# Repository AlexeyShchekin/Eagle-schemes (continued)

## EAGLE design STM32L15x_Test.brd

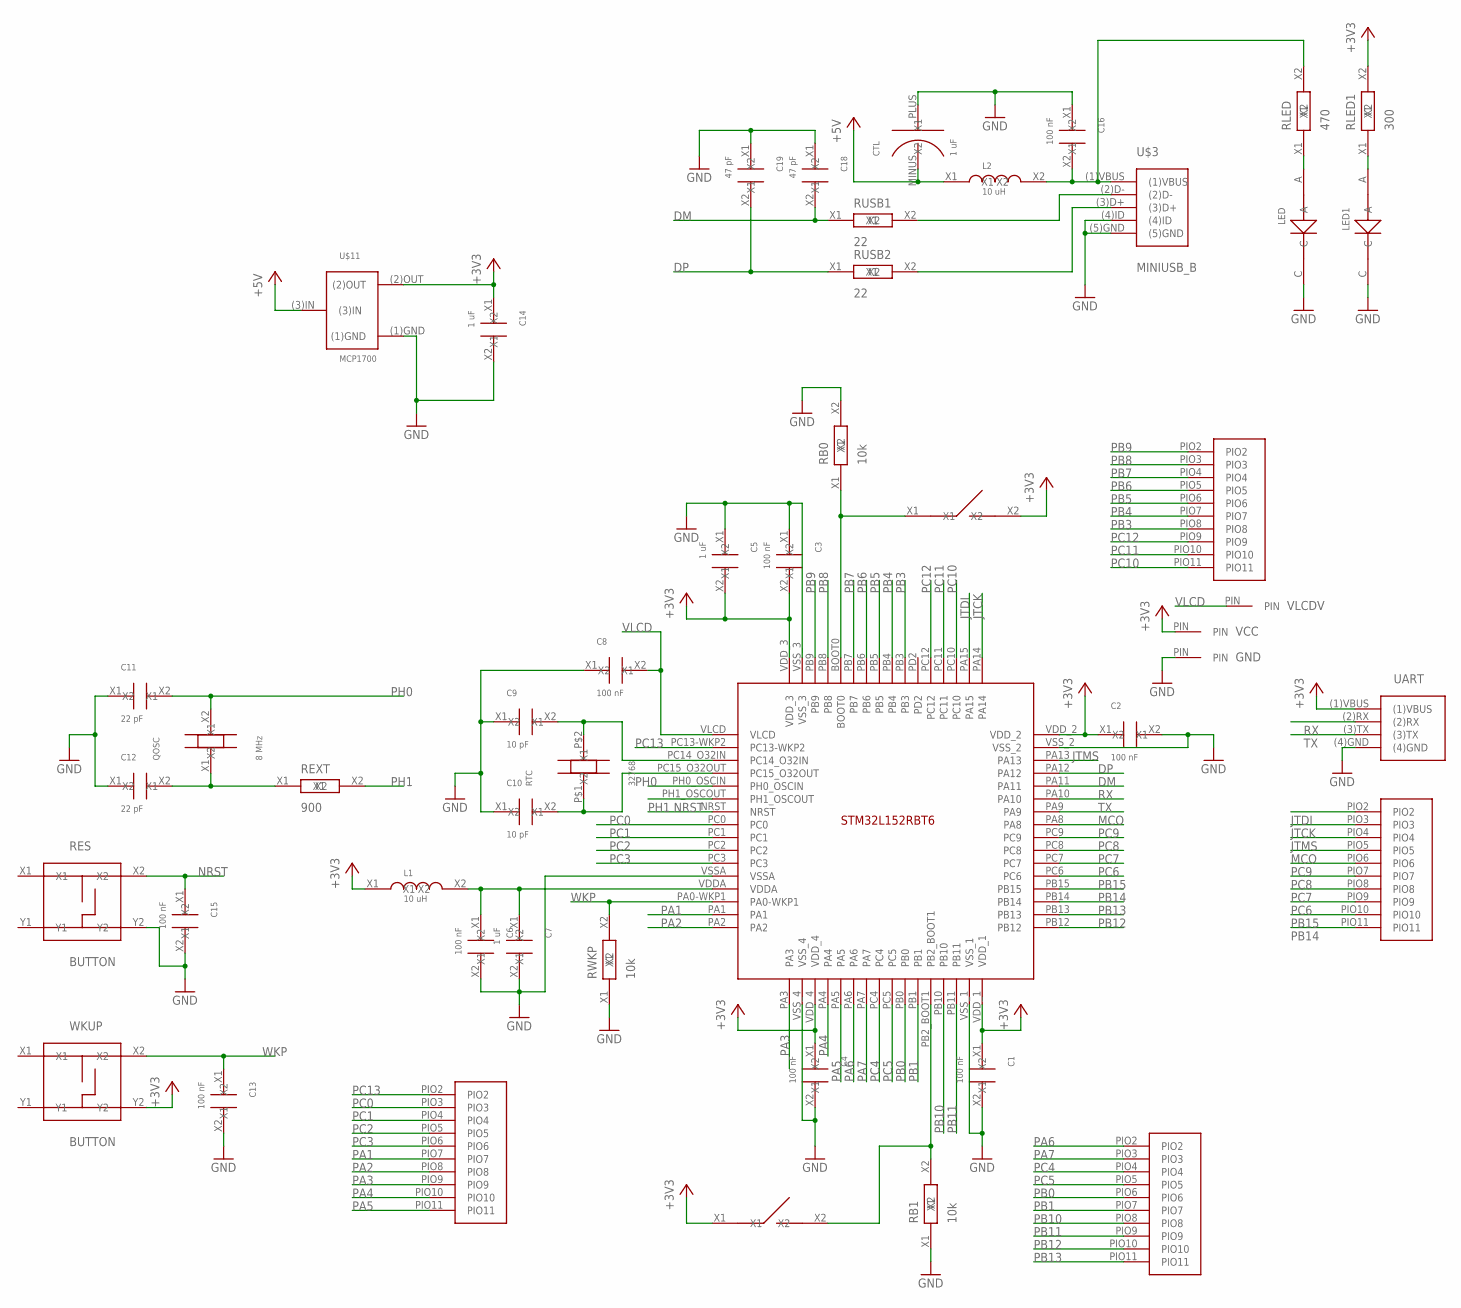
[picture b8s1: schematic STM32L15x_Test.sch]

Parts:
C1, C2, C3, C4, C6, C8, C13, C15, C16: 100 nF; SMD_2.1X1.25
C5, C7, C14: 1 uF; SMD_2.1X1.25
C9, C10: 10 pF; SMD_2.1X1.25
C11, C12: 22 pF; SMD_2.1X1.25
C18, C19: 47 pF; SMD_2.1X1.25
CTL: 1 uF; C_SMD_TA_A
GND: PIN
L1, L2: 10 uH; SMD_2.1X1.25
LED, LED1: LED0805; SMD0805
QOSC: 8 MHz; QUARTZ_SMD
RB0, RB1: 10k; SMD_2.1X1.25
RES: BUTTON
REXT: 900; SMD_2.1X1.25
RLED: 470; SMD_2.1X1.25
RLED1: 300; SMD_2.1X1.25
RTC: 32768; QUARTZ_CYL
RUSB1, RUSB2: 22; SMD_2.1X1.25
RWKP: 10k; SMD_2.1X1.25
U$1: STM32L15XRBT6; STM32L152RBT6
U$2, U$5, U$6, U$7: PIO_10
U$3: MINIUSB_B
U$8, U$9: DIP_1
U$11: MCP1700
UART: USART
VCC: PIN
VLCDV: PIN
WKUP: BUTTON

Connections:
+3V3: C1.X1, C2.X1, C3.X2, C4.X1, C5.X2, C14.X1, L1.X1, RLED1.X2, U$1.VDD_1, U$1.VDD_2, U$1.VDD_3, U$1.VDD_4, U$8.X2, U$9.X1, U$11.(2)OUT, UART.(1)VBUS, VCC.PIN, WKUP.Y2
+5V: CTL.MINUS (X1), L2.X1, U$11.(3)IN
BOOT0: RB0.X1, U$1.BOOT0, U$8.X1
BOOT1: RB1.X2, U$1.PB2_BOOT1, U$9.X2
DM: C18.X2, RUSB1.X1, U$1.PA11
DP: C19.X2, RUSB2.X1, U$1.PA12
GND: C1.X2, C2.X2, C3.X1, C4.X2, C5.X1, C6.X2, C7.X2, C8.X1, C9.X1, C10.X1, C11.X1, C12.X1, C13.X2, C14.X2, C15.X2, C16.X1, C18.X1, C19.X1, CTL.PLUS (X2), GND.PIN, LED.C, LED1.C, RB0.X2, RB1.X1, RES.Y2, RWKP.X1, U$1.VSSA, U$1.VSS_1, U$1.VSS_2, U$1.VSS_3, U$1.VSS_4, U$3.(4)ID, U$3.(5)GND, U$11.(1)GND, UART.(4)GND
JTCK: U$1.PA14, U$6.PIO3
JTDI: U$1.PA15, U$6.PIO2
JTMS: U$1.PA13, U$6.PIO4
MCO: U$1.PA8, U$6.PIO5
unnamed: C6.X1, C7.X1, L1.X2, U$1.VDDA
unnamed: C9.X2, RTC.P$2 (X2), U$1.PC14_O32IN
unnamed: C10.X2, RTC.P$1 (X1), U$1.PC15_O32OUT
unnamed: C12.X2, QOSC.X1, REXT.X1
unnamed: C16.X2, L2.X2, RLED.X2, U$3.(1)VBUS
unnamed: RUSB1.X2, U$3.(2)D-
unnamed: RUSB2.X2, U$3.(3)D+
unnamed: LED.A, RLED.X1
unnamed: LED1.A, RLED1.X1
NRST: C15.X1, RES.X2, U$1.NRST
PA1: U$1.PA1, U$2.PIO7
PA2: U$1.PA2, U$2.PIO8
PA3: U$1.PA3, U$2.PIO9
PA4: U$1.PA4, U$2.PIO10
PA5: U$1.PA5, U$2.PIO11
PA6: U$1.PA6, U$5.PIO2
PA7: U$1.PA7, U$5.PIO3
PB0: U$1.PB0, U$5.PIO6
PB1: U$1.PB1, U$5.PIO7
PB3: U$1.PB3, U$7.PIO8
PB4: U$1.PB4, U$7.PIO7
PB5: U$1.PB5, U$7.PIO6
PB6: U$1.PB6, U$7.PIO5
PB7: U$1.PB7, U$7.PIO4
PB8: U$1.PB8, U$7.PIO3
PB9: U$1.PB9, U$7.PIO2
PB10: U$1.PB10, U$5.PIO8
PB11: U$1.PB11, U$5.PIO9
PB12: U$1.PB12, U$5.PIO10
PB13: U$1.PB13, U$5.PIO11
PB14: U$1.PB14, U$6.PIO11
PB15: U$1.PB15, U$6.PIO10
PC0: U$1.PC0, U$2.PIO3
PC1: U$1.PC1, U$2.PIO4
PC2: U$1.PC2, U$2.PIO5
PC3: U$1.PC3, U$2.PIO6
PC4: U$1.PC4, U$5.PIO4
PC5: U$1.PC5, U$5.PIO5
PC6: U$1.PC6, U$6.PIO9
PC7: U$1.PC7, U$6.PIO8
PC8: U$1.PC8, U$6.PIO7
PC9: U$1.PC9, U$6.PIO6
PC10: U$1.PC10, U$7.PIO11
PC11: U$1.PC11, U$7.PIO10
PC12: U$1.PC12, U$7.PIO9
PC13: U$1.PC13-WKP2, U$2.PIO2
PH0: C11.X2, QOSC.X2, U$1.PH0_OSCIN
PH1: REXT.X2, U$1.PH1_OSCOUT
RX: U$1.PA10, UART.(2)RX
TX: U$1.PA9, UART.(3)TX
VLCD: C8.X2, U$1.VLCD, VLCDV.PIN
WKP: C13.X1, RWKP.X2, U$1.PA0-WKP1, WKUP.X2

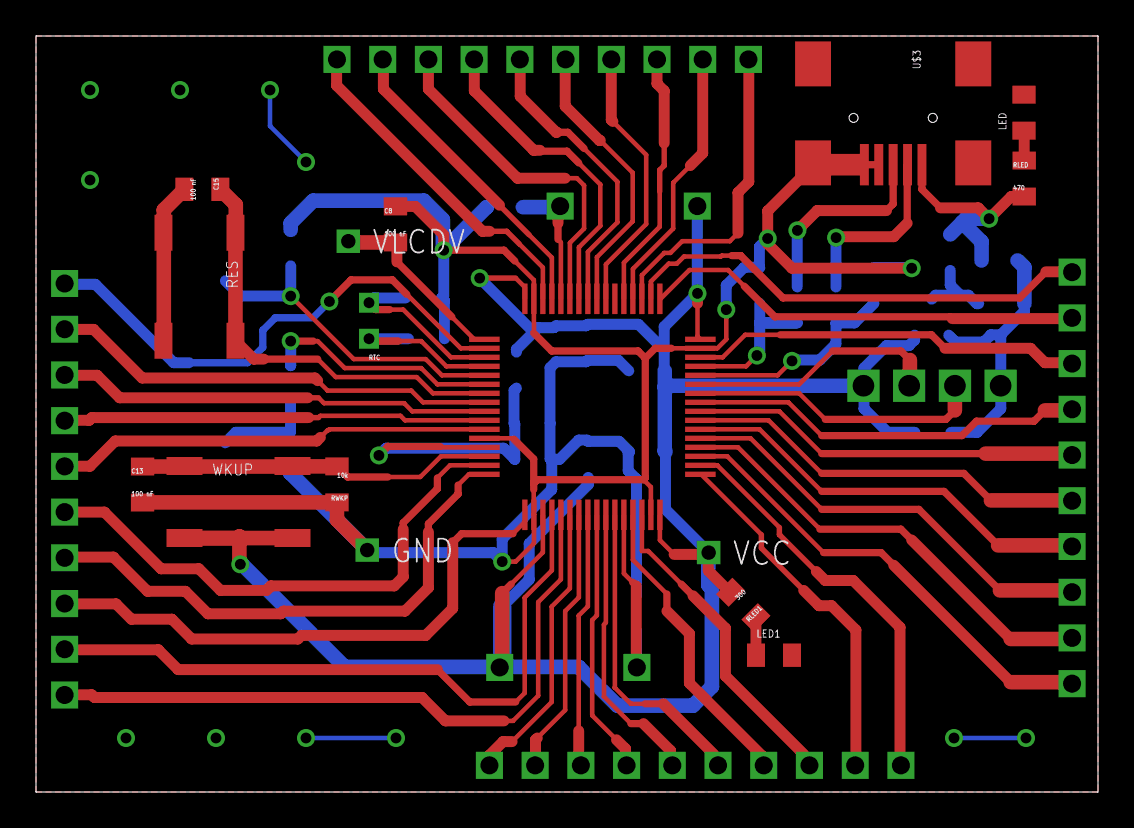
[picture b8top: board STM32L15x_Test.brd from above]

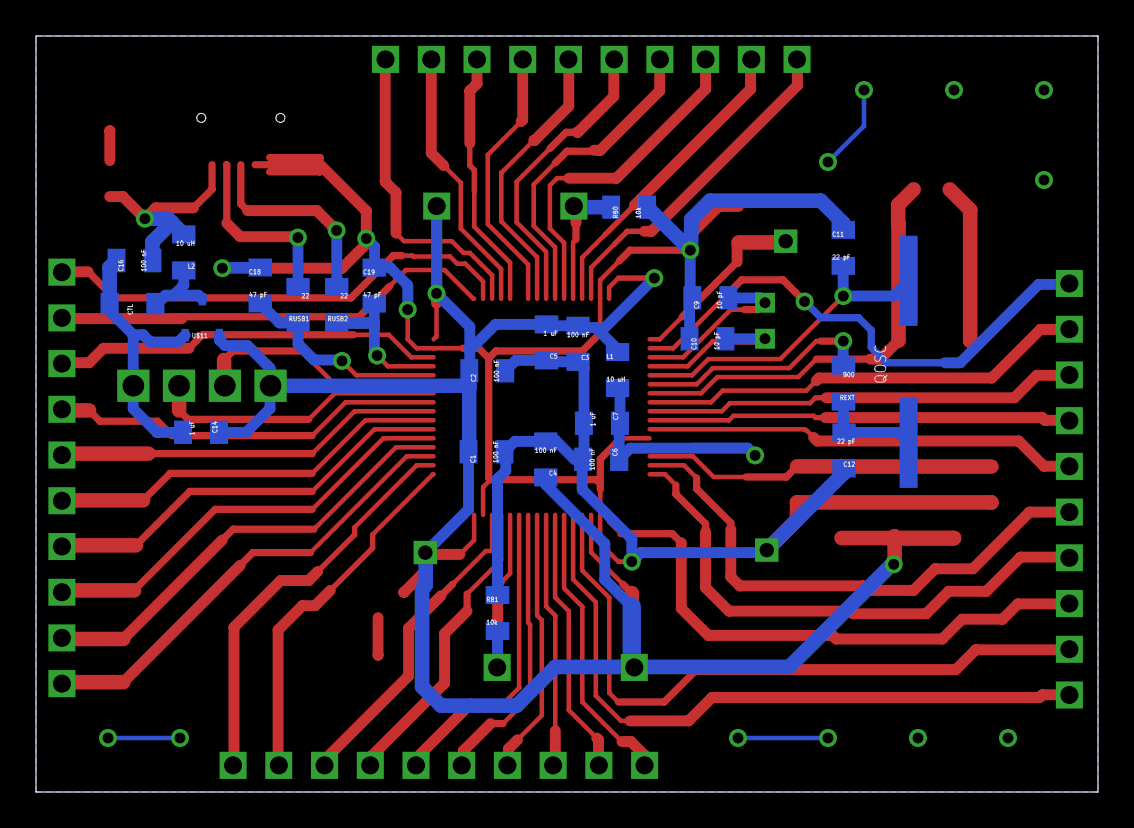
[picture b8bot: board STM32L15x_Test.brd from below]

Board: 2 copper layers, 59.0 x 42.0 mm, 48 parts (25 on the bottom side), 63 nets.
